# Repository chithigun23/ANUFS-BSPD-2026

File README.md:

# ANUFS BSPD 2026

**Brake System Plausibility Device — analog detection, timed qualification, latched shutdown.**

This board monitors two throttle-position signals (TPS1/TPS2) and brake pressure (BPS). A persistent sensor-range fault, or sustained hard braking with throttle above 10%, removes the board's supply to the vehicle shutdown circuit.

## System architecture

## How a trip happens

1. **Condition the inputs.** TVS Diodes protect the sensor lines; pull-downs bias disconnected inputs low, as required by rules. R1/C2, R10/C3 and R15/C5 RC filter TPS1, TPS2 and BPS, respectively (5.49 kΩ / 1 µF).
2. **Check two independent fault paths.** U2/U4 compare each sensor with `V_THL` and `V_THH`. In parallel, U1 detects hard braking **AND** either TPS channel above its calibrated 10% threshold. TPS2 uses the opposite comparator polarity to TPS1, matching the schematic's opposite sensor slopes.
3. **Require persistence.** U3 qualifies each sensor-range fault for approximately **100 ms**, or `HB&10%` for approximately **1 second**. A brief excursion that recovers sufficiently before the timing threshold does not trip the latch; RC history affects closely spaced excursions.
4. **Latch the fault.** U3's open-collector outputs share `FAULT`. Any qualified fault pulls this normally high net low, asserting U5's asynchronous clear. U5 Q falls and stays low after the original fault disappears.
5. **Remove shutdown-circuit power.** Low `OUTPUT` turns Q1 off; R30 pulls Q2's gate toward its source, turning the P-channel switch off. The board stops supplying +12 V to `SC_OUT` on J1 pin 5. External vehicle circuitry determines the resulting shutdown action.

### Operating states

| Condition | Qualified `FAULT` | U5 Q / `OUTPUT` | `SC_OUT` supply |
|---|---|---|---|
| Initialized, healthy, no previous trip | High | High | Enabled |
| Fault present, timer has not reached threshold | High | Remains high if previously enabled | Enabled |
| Either fault path reaches its timer threshold | Low | Forced low | Disabled |
| Sensor condition recovers after a trip | Returns high after timer recovery | Remains low | Disabled |
| Power cycled with faults absent | Power-on preset initializes U5 | Returns high | Enabled after initialization |

The U7 Schmitt-trigger circuit with R32/C19/C20 generates the power-on preset. This design does not use a software reset or automatically re-enable just because a fault clears.

## Supporting circuits

| Block | Implementation |
|---|---|
| Logic supply | U6 LM1117-5.0 regulates +12 V to +5 V; D5 provides supply transient suppression. |
| Sensor limits | SW1/SW2 select fixed or variable window references. Fixed net names are `+0V45` and `+4V7`; RV4/RV5 provide adjustable alternatives. |
| Operating thresholds | RV1 sets `HB_THRESH`; RV2/RV3 set `TPS1_THRESH` / `TPS2_THRESH`. Calibrate these against the actual sensors. |
| Timing reference | `+2V5` feeds U3; sensor timers use 150 kΩ / 1 µF; overlap timing uses R7 + R8 = 300 kΩ with C1 = 4.7 µF. |
| Indicators | U8/U9 buffer condition indicators D10–D15. U5's complementary output drives latch indicator D9 through R39. |

### J1 interface

| Pin | Net | Role |
|---|---|---|
| 1 | `+12V` | Board and switched-output supply |
| 2 | Unconnected | No connection |
| 3 | `GND` | Board ground |
| 4 | `/SENS_0V` | Sensor return, joined to GND through R46 (0 Ω) |
| 5 | `SC_OUT` | Switched shutdown-circuit supply |
| 6 | `BPS_RAW` | Brake-pressure input |
| 7 | `TPS2_RAW` | Throttle-position channel 2 |
| 8 | `TPS1_RAW` | Throttle-position channel 1 |

## Design files

- [KiCad project](bspd-kicad/bspd.kicad_pro)
- [Schematic](bspd-kicad/bspd.kicad_sch)
- [PCB layout](bspd-kicad/bspd.kicad_pcb)
- [Bill of materials](BSPD_DigiKey_BOM.xlsx)

## Attribution

Animation generated using [Dashmotion](https://github.com/csthink/dashmotion) (MIT); attribution is retained in [docs/DASHMOTION-LICENSE.txt](docs/DASHMOTION-LICENSE.txt). The diagram assets have no external runtime dependencies.

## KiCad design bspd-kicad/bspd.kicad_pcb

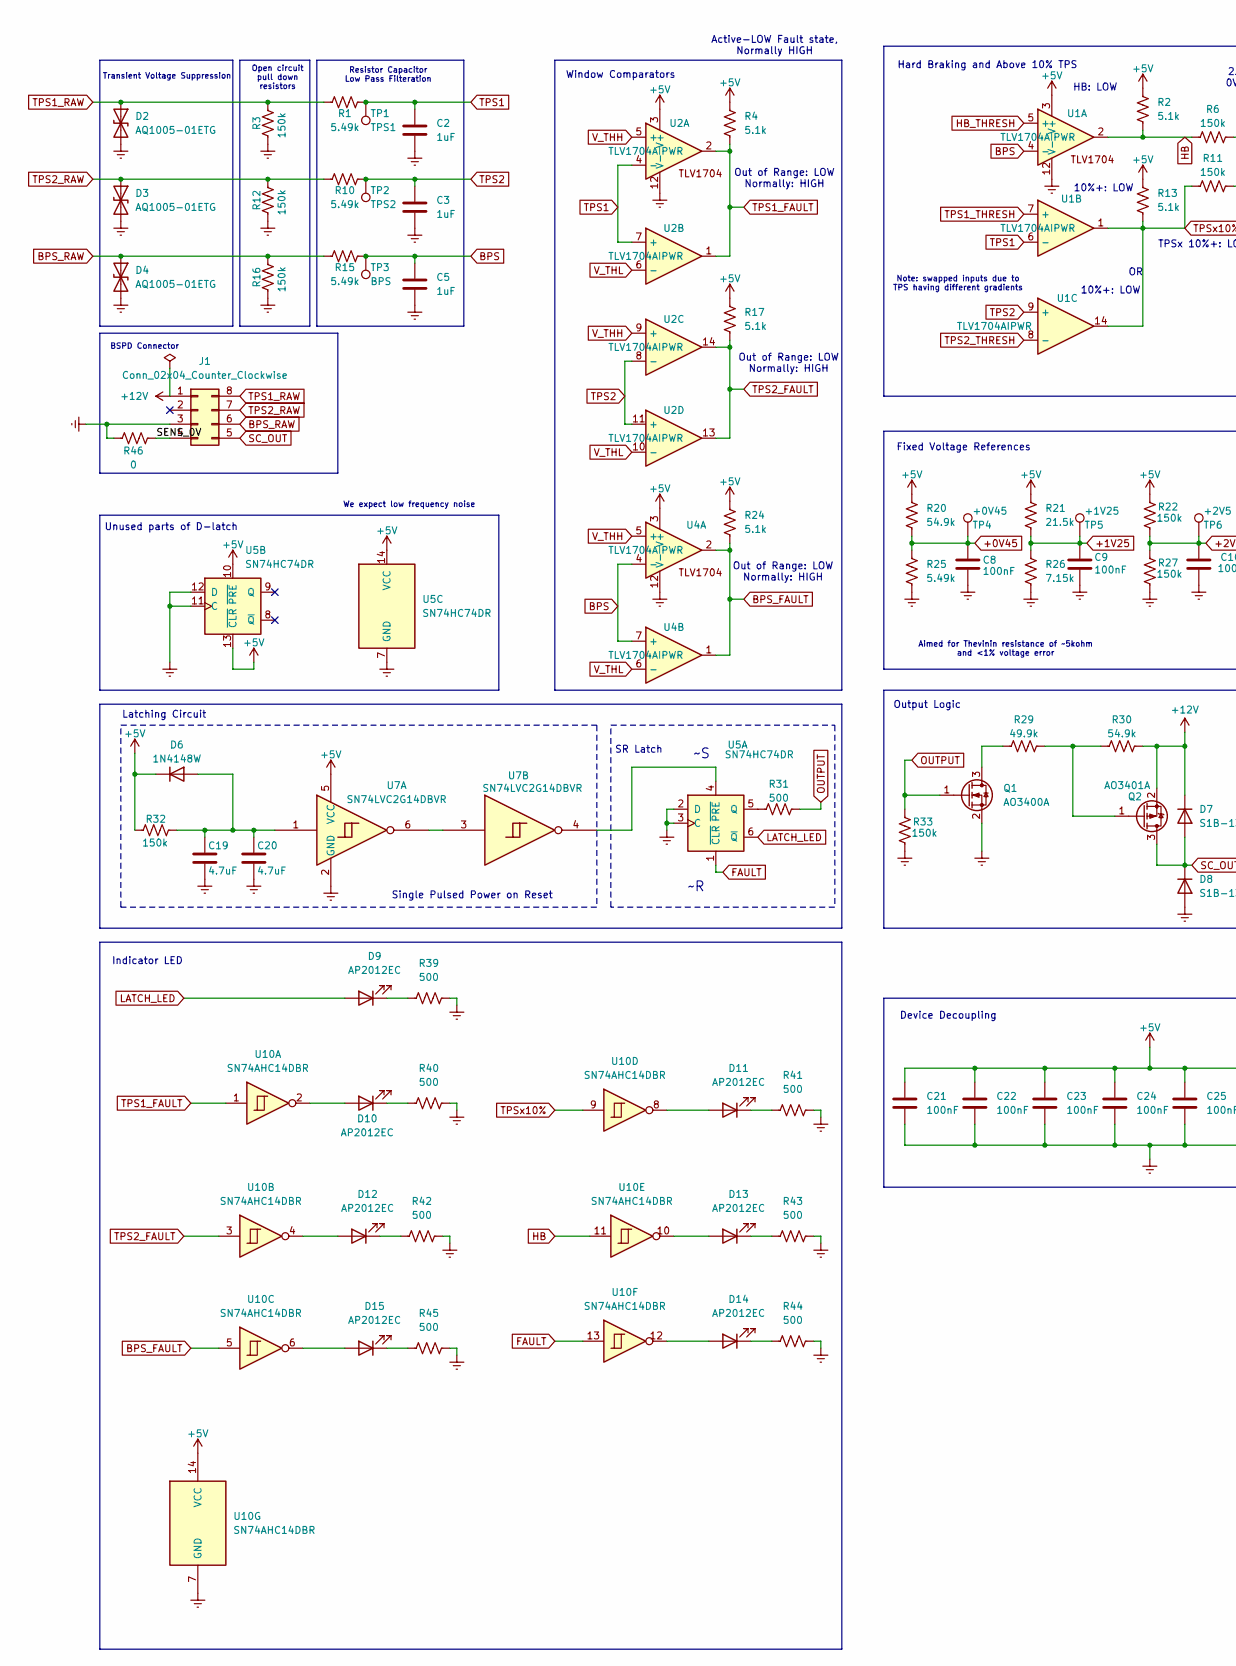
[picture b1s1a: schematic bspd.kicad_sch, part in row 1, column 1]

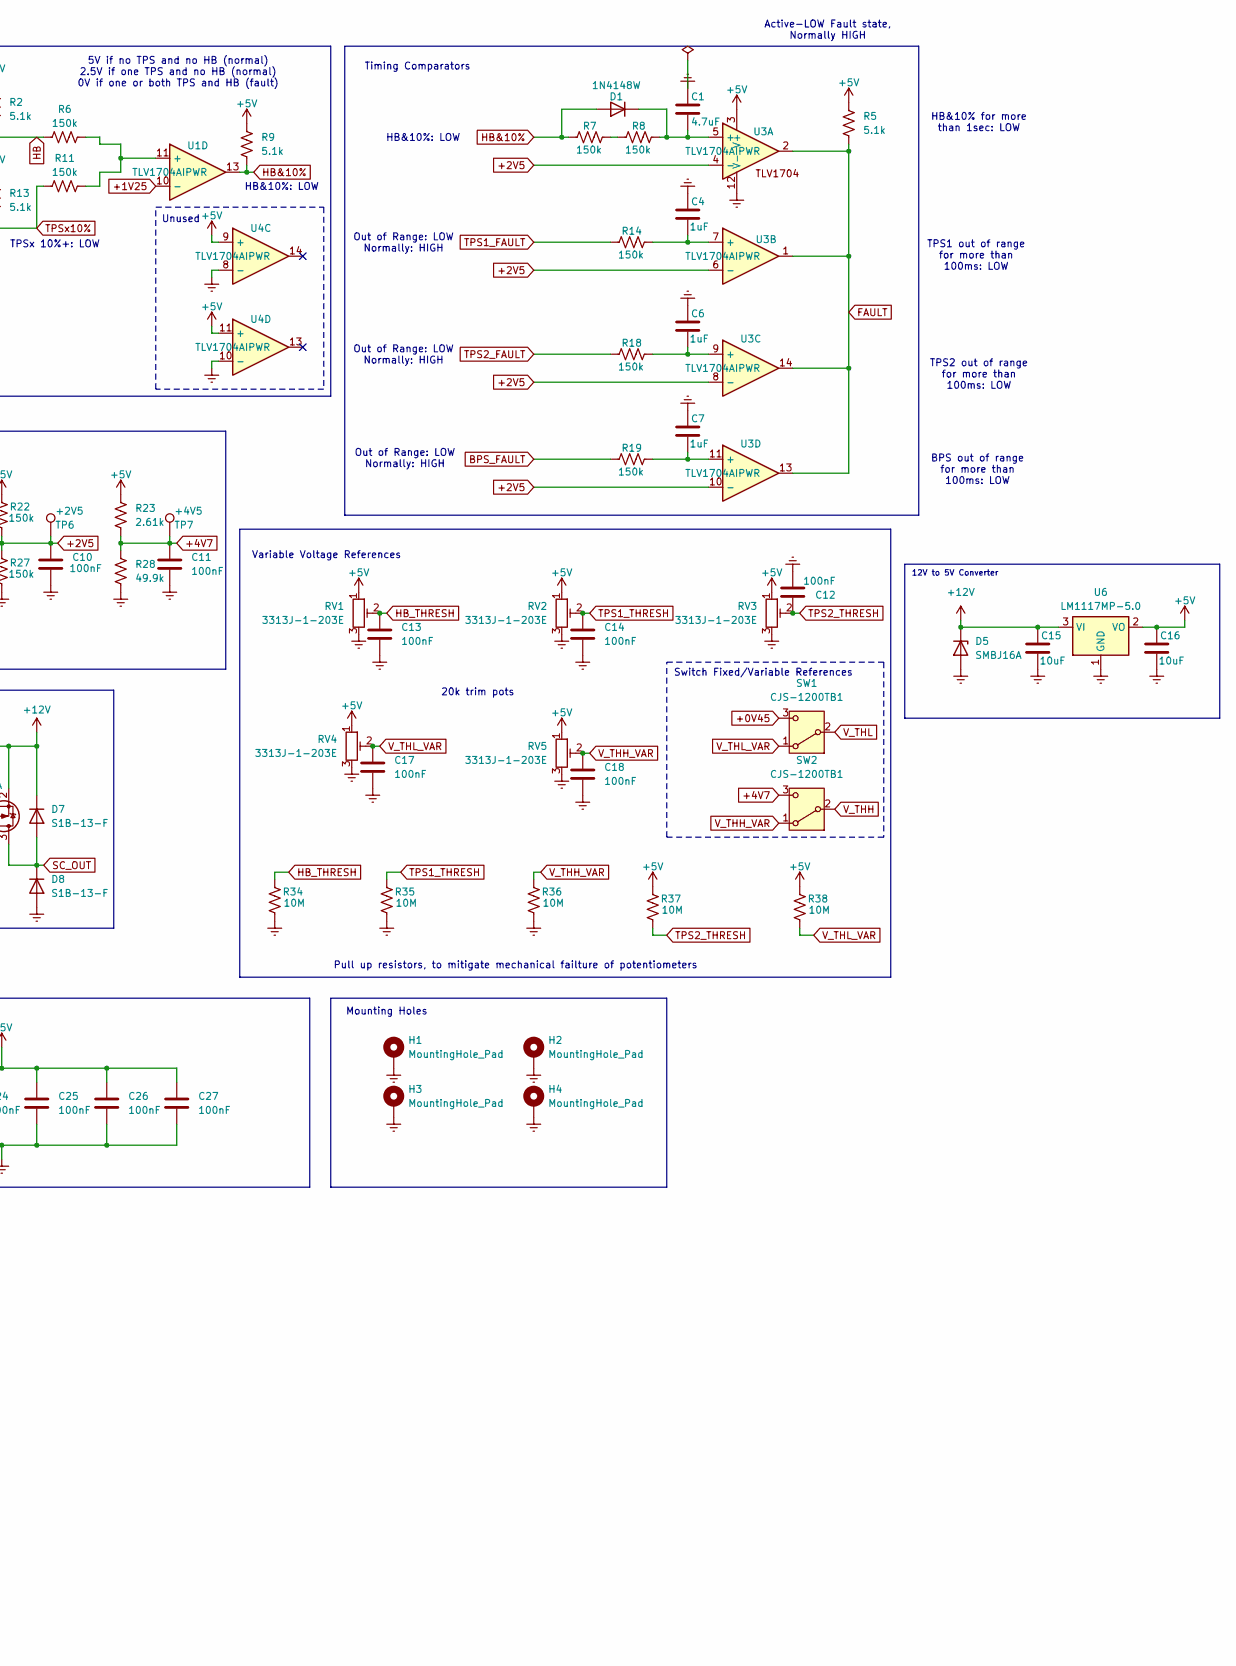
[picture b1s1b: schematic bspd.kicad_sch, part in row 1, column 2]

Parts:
C1, C19, C20: 4.7uF; C_0805_2012Metric_Pad1.18x1.45mm_HandSolder; Voltage 16V; Tolerance 10%
C2, C3, C4, C5, C6, C7: 1uF; C_0805_2012Metric_Pad1.18x1.45mm_HandSolder; Voltage 16V; Tolerance 10%
C8, C9, C10, C11, C12, C13, C14, C17, C18, C21, C22, C23, C24, C25, C26, C27: 100nF; C_0805_2012Metric_Pad1.18x1.45mm_HandSolder; Voltage 16V; Tolerance 10%
C15: 10uF; C_0805_2012Metric_Pad1.18x1.45mm_HandSolder; Voltage 25V; Tolerance 10%
C16: 10uF; C_0805_2012Metric_Pad1.18x1.45mm_HandSolder; Voltage 16V; Tolerance 10%
D1, D6: 1N4148W; D_SOD-123
D2, D3, D4: AQ1005-01ETG; D_SOD-882; MPN AQ1005-01ETG
D5: SMBJ16A; MPN SMBJ16A; LCSC Part C151254
D7, D8: S1B-13-F; MPN S1B-13-F; LCSC Part C156295
D9, D10, D11, D12, D13, D14, D15: AP2012EC; MPN AP2012EC
H1, H2, H3, H4: MountingHole_Pad; MountingHole_3.2mm_M3_ISO14580_Pad
J1: Conn_02x04_Counter_Clockwise; WirePad_2x04_P3.0mm
Q1: AO3400A; SOT-23
Q2: AO3401A; SOT-23
R1, R10, R15, R25: 5.49k; R_0805_2012Metric_Pad1.20x1.40mm_HandSolder; Tolerance 1%
R2, R4, R5, R9, R13, R17, R24: 5.1k; R_0805_2012Metric_Pad1.20x1.40mm_HandSolder; Tolerance 1%
R3, R6, R7, R8, R11, R12, R14, R16, R18, R19, R22, R27, R32, R33: 150k; R_0805_2012Metric_Pad1.20x1.40mm_HandSolder; Tolerance 1%
R20, R30: 54.9k; R_0805_2012Metric_Pad1.20x1.40mm_HandSolder; Tolerance 1%
R21: 21.5k; R_0805_2012Metric_Pad1.20x1.40mm_HandSolder; Tolerance 1%
R23: 2.61k; R_0805_2012Metric_Pad1.20x1.40mm_HandSolder; Tolerance 1%
R26: 7.15k; R_0805_2012Metric_Pad1.20x1.40mm_HandSolder; Tolerance 1%
R28, R29: 49.9k; R_0805_2012Metric_Pad1.20x1.40mm_HandSolder; Tolerance 1%
R31, R39, R40, R41, R42, R43, R44, R45: 500; R_0805_2012Metric_Pad1.20x1.40mm_HandSolder; Tolerance 1%
R34, R35, R36, R37, R38: 10M; R_0805_2012Metric_Pad1.20x1.40mm_HandSolder; Tolerance 1%
R46: 0; R_0805_2012Metric_Pad1.20x1.40mm_HandSolder
RV1, RV2, RV3, RV4, RV5: 3313J-1-203E; Tolerance 20%; MPN 3313J-1-203E; LCSC Part C124621
SW1, SW2: CJS-1200TB1; MPN CJS-1200TB1; LCSC Part C2921631
TP1: TPS1; TestPoint_Keystone_5000-5004_Miniature
TP2: TPS2; TestPoint_Keystone_5000-5004_Miniature
TP3: BPS; TestPoint_Keystone_5000-5004_Miniature
TP4: +0V45; TestPoint_Keystone_5000-5004_Miniature
TP5: +1V25; TestPoint_Keystone_5000-5004_Miniature
TP6: +2V5; TestPoint_Keystone_5000-5004_Miniature
TP7: +4V5; TestPoint_Keystone_5000-5004_Miniature
U1, U2, U3, U4: TLV1704AIPWR; TLV1704; MPN TLV1704AIPWR
U5: SN74HC74DR; MPN SN74HC74DR; LCSC Part C6762
U6: LM1117MP-5.0; SOT-223-3_TabPin2
U7: SN74LVC2G14DBVR; MPN SN74LVC2G14DBVR; LCSC Part C12401
U10: SN74AHC14DBR

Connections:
+0V45: C8.1, R20.2, R25.1, SW1.3 (C), TP4.1 (1_1)
+1V25: C9.1, R21.2, R26.1, TP5.1 (1_1), U1.10 (-)
+2V5: C10.1, R22.1, R27.2, TP6.1 (1_1), U3.4 (-), U3.6 (-), U3.8 (-), U3.10 (-)
+4V7: C11.1, R23.2, R28.1, SW2.3 (C), TP7.1 (1_1)
+5V: C16.2, C21.1, C22.1, C23.1, C24.1, C25.1, C26.1, C27.1, D6.1 (K), R2.1, R4.1, R5.1, R9.1, R13.1, R17.1, R20.1, R21.1, R22.2, R23.1, R24.1, R32.1, R37.2, R38.2, RV1.1, RV2.1, RV3.1, RV4.1, RV5.1, U1.3 (V+), U2.3 (V+), U3.3 (V+), U4.3 (V+), U4.9 (+), U4.11 (+), U5.10 (~PRE), U5.13 (~CLR), U5.14 (VCC), U6.2 (VO), U7.5 (VCC), U10.14 (VCC)
+12V: C15.2, D5.1 (K), D7.1 (K), J1.1, Q2.2 (S), R30.1, U6.3 (VI)
/SENS_0V: J1.4, R46.2
BPS: C5.1, R15.2, TP3.1 (1_1), U1.4 (-), U4.4 (-), U4.7 (+)
BPS_FAULT: R19.1, R24.2, U4.1, U4.2, U10.5
BPS_RAW: D4.1 (A1), J1.6, R15.1, R16.2
FAULT: R5.2, U3.1, U3.2, U3.13, U3.14, U5.1 (~CLR), U10.13
GND: C1.2, C2.2, C3.2, C4.2, C5.2, C6.2, C7.2, C8.2, C9.2, C10.2, C11.2, C12.2, C13.2, C14.2, C15.1, C16.1, C17.2, C18.2, C19.1, C20.1, C21.2, C22.2, C23.2, C24.2, C25.2, C26.2, C27.2, D2.2 (A2), D3.2 (A2), D4.2 (A2), D5.2 (A), D8.2 (A), H1.1 (1_1), H2.1 (1_1), H3.1 (1_1), H4.1 (1_1), J1.3, Q1.2 (S), R3.1, R12.1, R16.1, R25.2, R26.2, R27.1, R28.2, R33.1, R34.1, R35.1, R36.1, R39.2, R40.2, R41.2, R42.2, R43.2, R44.2, R45.2, R46.1, RV1.3, RV2.3, RV3.3, RV4.3, RV5.3, U1.12 (V-), U2.12 (V-), U3.12 (V-), U4.8 (-), U4.10 (-), U4.12 (V-), U5.2 (D), U5.3 (C), U5.7 (GND), U5.11 (C), U5.12 (D), U6.1 (GND), U7.2 (GND), U10.7 (GND)
HB: R2.2, R6.2, U1.2, U10.11
HB&10%: D1.2 (A), R7.1, R9.2, U1.13
HB_THRESH: C13.1, R34.2, RV1.2, U1.5 (+)
LATCH_LED: D9.2 (A), U5.6 (~Q)
unnamed: C1.1, D1.1 (K), R8.2, U3.5 (+)
unnamed: C19.2, C20.2, D6.2 (A), R32.2, U7.1
unnamed: D9.1 (K), R39.1
unnamed: D10.2 (A), U10.2
unnamed: D10.1 (K), R40.1
unnamed: D11.2 (A), U10.8
unnamed: D11.1 (K), R41.1
unnamed: D12.2 (A), U10.4
unnamed: D12.1 (K), R42.1
unnamed: D13.2 (A), U10.10
unnamed: D13.1 (K), R43.1
unnamed: D14.2 (A), U10.12
unnamed: D14.1 (K), R44.1
unnamed: D15.2 (A), U10.6
unnamed: D15.1 (K), R45.1
unnamed: Q1.3 (D), R29.1
unnamed: Q2.1 (G), R29.2, R30.2
unnamed: R7.2, R8.1
unnamed: R6.1, R11.1, U1.11 (+)
unnamed: C4.1, R14.2, U3.7 (+)
unnamed: C6.1, R18.2, U3.9 (+)
unnamed: C7.1, R19.2, U3.11 (+)
unnamed: R31.1, U5.5 (Q)
unnamed: U5.4 (~PRE), U7.4
unnamed: U7.3, U7.6
OUTPUT: Q1.1 (G), R31.2, R33.2
SC_OUT: D7.2 (A), D8.1 (K), J1.5, Q2.3 (D)
TPS1: C2.1, R1.2, TP1.1 (1_1), U1.6 (-), U2.4 (-), U2.7 (+)
TPS1_FAULT: R4.2, R14.1, U2.1, U2.2, U10.1
TPS1_RAW: D2.1 (A1), J1.8, R1.1, R3.2
TPS1_THRESH: C14.1, R35.2, RV2.2, U1.7 (+)
TPS2: C3.1, R10.2, TP2.1 (1_1), U1.9 (+), U2.8 (-), U2.11 (+)
TPS2_FAULT: R17.2, R18.1, U2.13, U2.14, U10.3
TPS2_RAW: D3.1 (A1), J1.7, R10.1, R12.2
TPS2_THRESH: C12.1, R37.1, RV3.2, U1.8 (-)
TPSx10%: R11.2, R13.2, U1.1, U1.14, U10.9
V_THH: SW2.2 (B), U2.5 (+), U2.9 (+), U4.5 (+)
V_THH_VAR: C18.1, R36.2, RV5.2, SW2.1 (A)
V_THL: SW1.2 (B), U2.6 (-), U2.10 (-), U4.6 (-)
V_THL_VAR: C17.1, R38.1, RV4.2, SW1.1 (A)

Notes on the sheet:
HB&10%: LOW
Single Pulsed Power on Reset
Unused parts of D-latch
Mounting Holes
Variable Voltage References
Note: swapped inputs due to TPS having different gradients
Out of Range: LOW Normally: HIGH
Resistor Capacitor Low Pass Filteration
Output Logic
Switch Fixed/Variable References
Indicator LED
Fixed Voltage References
Window Comparators
Aimed for Thevinin resistance of ~5kohm and <1% voltage error
Device Decoupling
Latching Circuit
SR Latch
HB: LOW
TPS1 out of range for more than 100ms: LOW
10%+: LOW
TPSx 10%+: LOW
We expect low frequency noise
Timing Comparators
BSPD Connector
HB&10% for more than 1sec: LOW
Active-LOW Fault state, Normally HIGH
20k trim pots
Pull up resistors, to mitigate mechanical failture of potentiometers
Open circuit pull down resistors
BPS out of range for more than 100ms: LOW
12V to 5V Converter
Hard Braking and Above 10% TPS
Unused
TPS2 out of range for more than 100ms: LOW
Transient Voltage Suppression
5V if no TPS and no HB (normal) 2.5V if one TPS and no HB (normal) 0V if one or both TPS and HB (fault)

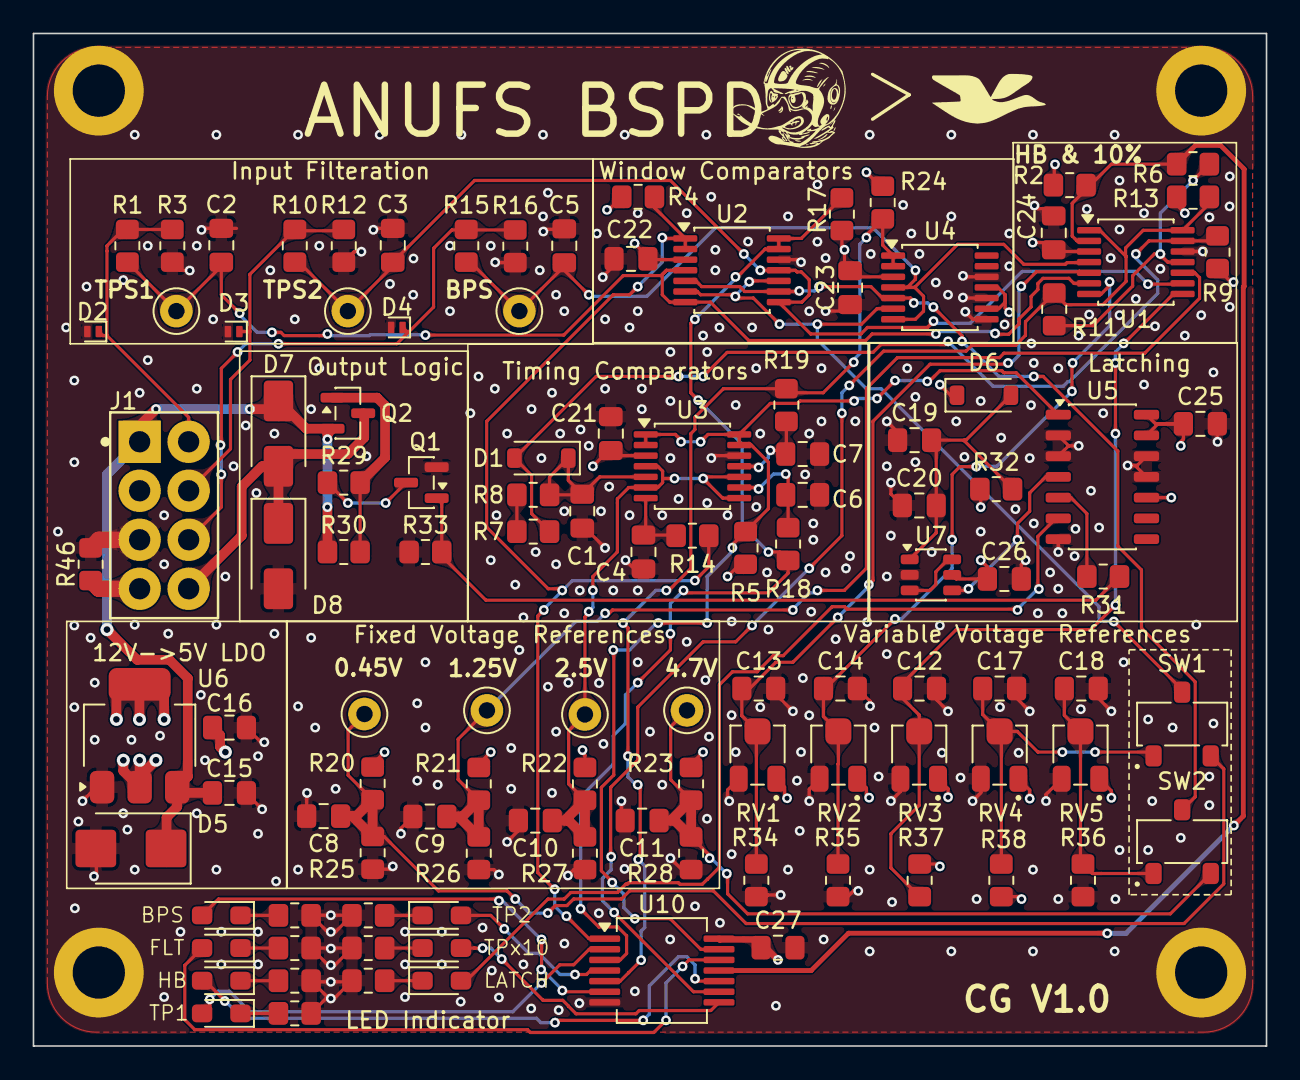
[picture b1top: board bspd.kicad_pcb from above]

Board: 4 copper layers, 75.5 x 62.0 mm, 117 parts (0 on the bottom side), 56 nets.

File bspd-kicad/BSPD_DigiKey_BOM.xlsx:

# | Reference(s) | Qty | Value | Package / Footprint | Manufacturer | Manufacturer Part Number (MPN) | DigiKey Part Number | Purchasing spec / action | Notes
1 | C1,C19,C20 | 3 | 4.7uF | C_0805_2012Metric_Pad1.18x1.45mm_HandSolder |  |  |  | TIMING CAP - X7R, 25V or 50V rating (NOT 6.3/10V) | Sets BSP-02 startup delay (C19||C20) and the 1 s trip timer (C1). Low-voltage-r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
2 | C2-C7 | 6 | 1uF | C_0805_2012Metric_Pad1.18x1.45mm_HandSolder |  |  |  | X7R, 16V+ | Comparator input filters.
3 | C8-C14,C17,C18,C21-C28 | 17 | 100nF | C_0805_2012Metric_Pad1.18x1.45mm_HandSolder |  |  |  | X7R, 25V/50V | Decoupling. Any reputable 0805 X7R.
4 | C15,C16 | 2 | 10uF | C_0805_2012Metric_Pad1.18x1.45mm_HandSolder |  |  |  | C16 IS SPECIAL - see notes tab | C15 (12V input) any X7R >=25V. C16 is the LM1117 OUTPUT cap: TI requires ESR 0.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
5 | D1,D6 | 2 | 1N4148W | D_SOD-123 | Diodes Incorporated | 1N4148W-7-F |  |  | MPN inferred from value - verify before ordering.
6 | D2-D4 | 3 | AQ1005-01ETG | D_SOD-882 | Littelfuse | AQ1005-01ETG
7 | D5 | 1 | SMBJ16A | SMBJ16A | Littelfuse | SMBJ16A
8 | D7,D8 | 2 | S1B-13-F | S1B-13-F | Diodes Incorporated | S1B-13-F
9 | D9-D15 | 7 | AP2012EC | AP2012EC | Kingbright | AP2012EC
10 | J1 | 1 | Conn_02x04_Counter_Clockwise | WirePad_2x04_P3.0mm |  |  |  | No part to buy | Bare through-hole wire pads - solder wires directly.
11 | Q1 | 1 | AO3400A | SOT-23 | Alpha & Omega | AO3400A |  |  | MPN inferred from value - verify before ordering.
12 | Q2 | 1 | AO3401A | SOT-23 | Alpha & Omega | AO3401A |  |  | MPN inferred from value - verify before ordering.
13 | R1,R10,R15,R25 | 4 | 5.49k | R_0805_2012Metric_Pad1.20x1.40mm_HandSolder |  |  |  | 0805, 1% (E96 value)
14 | R2,R4,R5,R9,R13,R17,R24 | 7 | 5.1k | R_0805_2012Metric_Pad1.20x1.40mm_HandSolder |  |  |  | 0805, 1% (E96 value)
15 | R3,R6-R8,R11,R12,R14,R16,R18,R19,R22,R27,R32,R33 | 14 | 150k | R_0805_2012Metric_Pad1.20x1.40mm_HandSolder |  |  |  | 0805, 1% (E96 value)
16 | R20,R30 | 2 | 54.9k | R_0805_2012Metric_Pad1.20x1.40mm_HandSolder |  |  |  | 0805, 1% (E96 value)
17 | R21 | 1 | 21.5k | R_0805_2012Metric_Pad1.20x1.40mm_HandSolder |  |  |  | 0805, 1% (E96 value)
18 | R23 | 1 | 2.61k | R_0805_2012Metric_Pad1.20x1.40mm_HandSolder |  |  |  | 0805, 1% (E96 value)
19 | R26 | 1 | 7.15k | R_0805_2012Metric_Pad1.20x1.40mm_HandSolder |  |  |  | 0805, 1% (E96 value)
20 | R28,R29 | 2 | 49.9k | R_0805_2012Metric_Pad1.20x1.40mm_HandSolder |  |  |  | 0805, 1% (E96 value)
21 | R31,R39-R45 | 8 | 500 | R_0805_2012Metric_Pad1.20x1.40mm_HandSolder |  |  |  | ORDER 499 ohm (E96 1%) or 510 ohm (E24 5%) | "500 ohm" is not a standard 1% value. These are LED series resistors (R39-R45) 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
22 | R34-R38 | 5 | 10M | R_0805_2012Metric_Pad1.20x1.40mm_HandSolder |  |  |  | 1% - high value, check availability | Threshold-node bleed resistors.
23 | RV1-RV5 | 5 | 3313J-1-203E | 3313J-1-103E | Bourns | 3313J-1-203E
24 | SW1,SW2 | 2 | CJS-1200TB1 | CJS-1200TB1 | Nidec Components | CJS-1200TB1
25 | TP1 | 1 | TPS1 | TestPoint_Keystone_5000-5004_Miniature |  |  |  | Optional - only if you want physical test pins | Keystone 5000-5004 miniature test point. Board works without them (bare pad).
26 | TP2 | 1 | TPS2 | TestPoint_Keystone_5000-5004_Miniature |  |  |  | Optional - only if you want physical test pins | Keystone 5000-5004 miniature test point. Board works without them (bare pad).
27 | TP3 | 1 | BPS | TestPoint_Keystone_5000-5004_Miniature |  |  |  | Optional - only if you want physical test pins | Keystone 5000-5004 miniature test point. Board works without them (bare pad).
28 | TP4 | 1 | +0V45 | TestPoint_Keystone_5000-5004_Miniature |  |  |  | Optional - only if you want physical test pins | Keystone 5000-5004 miniature test point. Board works without them (bare pad).
29 | TP5 | 1 | +1V25 | TestPoint_Keystone_5000-5004_Miniature |  |  |  | Optional - only if you want physical test pins | Keystone 5000-5004 miniature test point. Board works without them (bare pad).
30 | TP6 | 1 | +2V5 | TestPoint_Keystone_5000-5004_Miniature |  |  |  | Optional - only if you want physical test pins | Keystone 5000-5004 miniature test point. Board works without them (bare pad).
31 | TP7 | 1 | +4V5 | TestPoint_Keystone_5000-5004_Miniature |  |  |  | Optional - only if you want physical test pins | Keystone 5000-5004 miniature test point. Board works without them (bare pad).
32 | U1-U4 | 4 | TLV1704AIPWR | TLV1704 | Texas Instruments | TLV1704AIPWR
33 | U5 | 1 | SN74HC74DR | SN74HC74DR | Texas Instruments | SN74HC74DR
34 | U6 | 1 | LM1117MP-5.0 | SOT-223-3_TabPin2 | Texas Instruments | LM1117MP-5.0/NOPB |  |  | MPN inferred from value - verify before ordering.
35 | U7 | 1 | SN74LVC2G14DBVR | SN74LVC2G14DBVR | Texas Instruments | SN74LVC2G14DBVR
36 | U8,U9 | 2 | SN74LVC3G14DCUR | SN74LVC3G14DCUR | Texas Instruments | SN74LVC3G14DCUR
 | TOTAL PLACEMENTS | 114
